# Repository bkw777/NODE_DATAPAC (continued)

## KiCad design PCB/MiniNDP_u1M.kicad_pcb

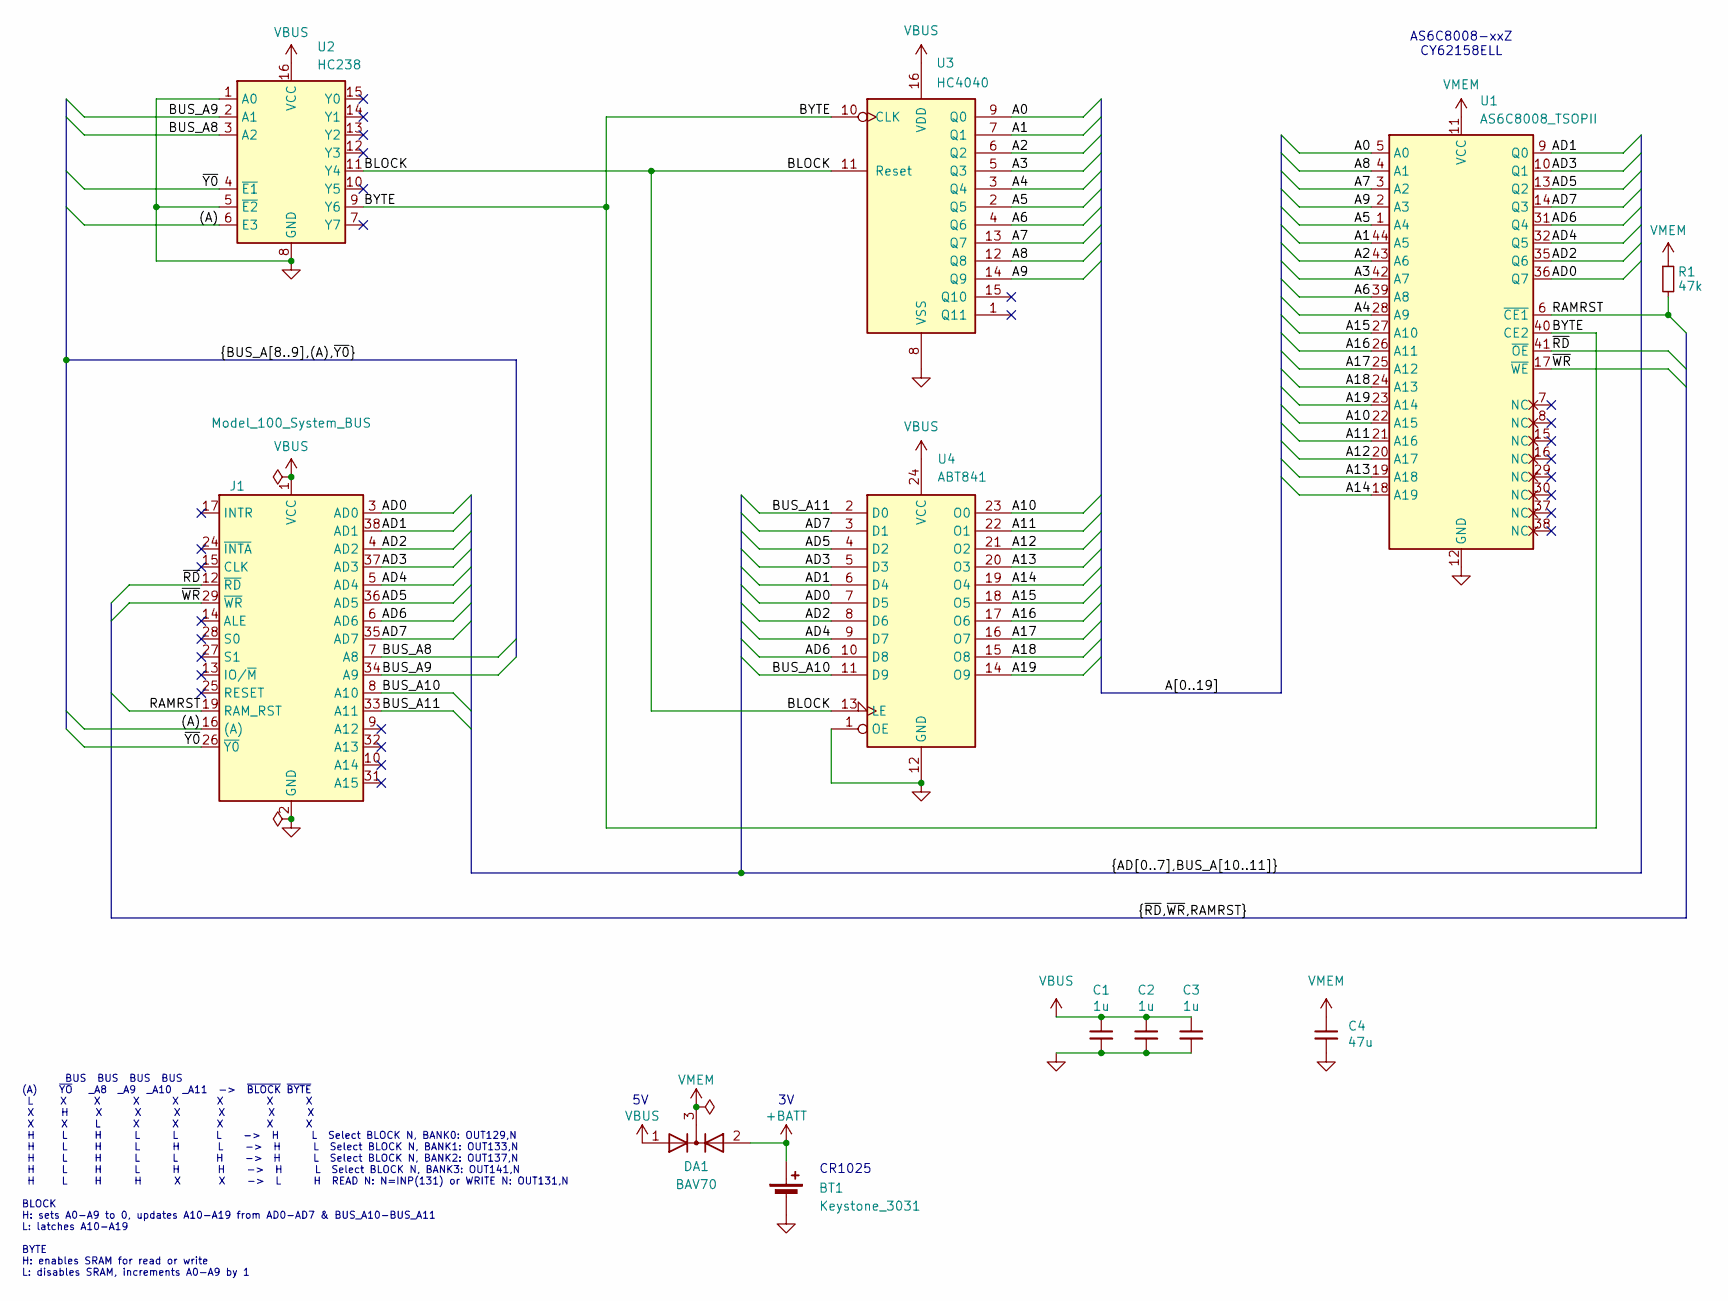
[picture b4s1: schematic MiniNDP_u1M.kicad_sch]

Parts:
BT1: Keystone_3031; MPN Keystone 3031
C1, C2, C3: 1u; C_0805; MPN CL21B105KAFNNNE
C4: 47u; C_1206; MPN C3216X5R1E476M160DC
DA1: BAV70; SOT-23; MPN BAV70-7-F
J1: Model_100_System_BUS; DIP-40_PCB; MPN 920-0172-01
R1: 47k; R_0805; MPN RMCF0805FT47K0
U1: AS6C8008_TSOPII; TSOP-II-44; MPN AS6C8008-55ZIN
U2: HC238; TSSOP-16; MPN 74HC238PW,118
U3: HC4040; TSSOP-16; MPN 74HC4040PW,118
U4: ABT841; TSSOP-24; MPN SN74ABT841APW

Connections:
+BATT: BT1.1 (+), DA1.2 (A)
/(A): J1.16 ((A)), U2.6 (E3)
/A0: U1.5 (A0), U3.9 (Q0)
/A1: U1.44 (A5), U3.7 (Q1)
/A2: U1.43 (A6), U3.6 (Q2)
/A3: U1.42 (A7), U3.5 (Q3)
/A4: U1.28 (A9), U3.3 (Q4)
/A5: U1.1 (A4), U3.2 (Q5)
/A6: U1.39 (A8), U3.4 (Q6)
/A7: U1.3 (A2), U3.13 (Q7)
/A8: U1.4 (A1), U3.12 (Q8)
/A9: U1.2 (A3), U3.14 (Q9)
/A10: U1.22 (A15), U4.23 (O0)
/A11: U1.21 (A16), U4.22 (O1)
/A12: U1.20 (A17), U4.21 (O2)
/A13: U1.19 (A18), U4.20 (O3)
/A14: U1.18 (A19), U4.19 (O4)
/A15: U1.27 (A10), U4.18 (O5)
/A16: U1.26 (A11), U4.17 (O6)
/A17: U1.25 (A12), U4.16 (O7)
/A18: U1.24 (A13), U4.15 (O8)
/A19: U1.23 (A14), U4.14 (O9)
/AD0: J1.3 (AD0), U1.36 (Q7), U4.7 (D5)
/AD1: J1.38 (AD1), U1.9 (Q0), U4.6 (D4)
/AD2: J1.4 (AD2), U1.35 (Q6), U4.8 (D6)
/AD3: J1.37 (AD3), U1.10 (Q1), U4.5 (D3)
/AD4: J1.5 (AD4), U1.32 (Q5), U4.9 (D7)
/AD5: J1.36 (AD5), U1.13 (Q2), U4.4 (D2)
/AD6: J1.6 (AD6), U1.31 (Q4), U4.10 (D8)
/AD7: J1.35 (AD7), U1.14 (Q3), U4.3 (D1)
/BLOCK: U2.11 (Y4), U3.11 (Reset), U4.13 (LE)
/BUS_A8: J1.7 (A8), U2.3 (A2)
/BUS_A9: J1.34 (A9), U2.2 (A1)
/BUS_A10: J1.8 (A10), U4.11 (D9)
/BUS_A11: J1.33 (A11), U4.2 (D0)
/BYTE: U1.40 (CE2), U2.9 (Y6), U3.10 (CLK)
/RAMRST: J1.19 (RAM_RST), R1.2, U1.6 (~CE1)
/~RD: J1.12 (~RD), U1.41 (~OE)
/~WR: J1.29 (~WR), U1.17 (~WE)
/~Y0: J1.26 (~Y0), U2.4 (~E1)
GND: BT1.2 (-), C1.2, C2.2, C3.2, C4.2, J1.2 (GND), J1.11 (GND), J1.18 (GND), J1.23 (GND), J1.30 (GND), J1.39 (GND), U1.12 (GND), U1.34 (GND), U2.1 (A0), U2.5 (~E2), U2.8 (GND), U3.8 (VSS), U4.1 (OE), U4.12 (GND)
VBUS: C1.1, C2.1, C3.1, DA1.1 (A), J1.1 (VCC), J1.40 (VCC), U2.16 (VCC), U3.16 (VDD), U4.24 (VCC)
VMEM: C4.1, DA1.3 (K), R1.1, U1.11 (VCC), U1.33 (VCC)

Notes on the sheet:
AS6C8008-xxZ CY62158ELL
BUS BUS BUS BUS (A) ~{YO} _A8 _A9 _A10 _A11 -> ~{BLOCK} ~{BYTE} L X X X X X X X X H X X X X X X X X L X X X X X H L H L L L -> H L Select BLOCK N, BANK0: OUT129,N H L H L H L -> H L Select BLOCK N, BANK1: OUT133,N H L H L L H -> H L Select BLOCK N, BANK2: OUT137,N H L H L H H -> H L Select BLOCK N,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
CR1025

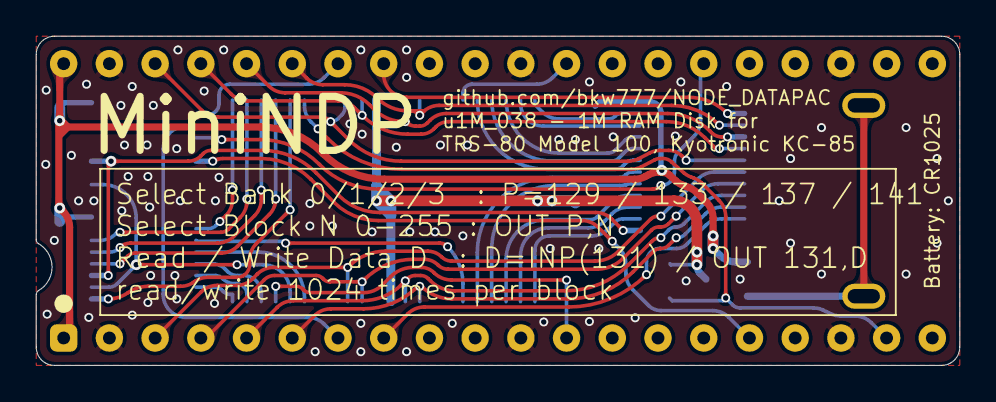
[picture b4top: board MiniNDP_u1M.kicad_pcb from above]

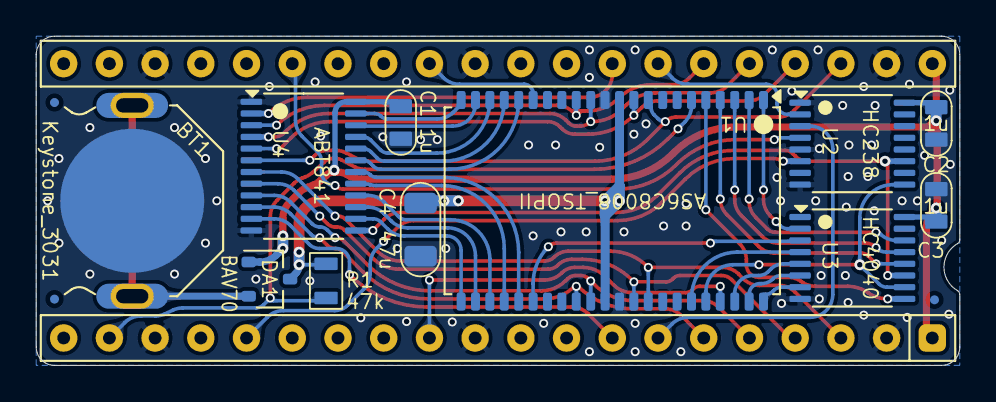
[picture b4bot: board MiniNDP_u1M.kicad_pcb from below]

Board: 2 copper layers, 51.3 x 18.3 mm, 15 parts (15 on the bottom side), 43 nets.

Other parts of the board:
F1, F2, F3: Fiducial_0.5_1.0

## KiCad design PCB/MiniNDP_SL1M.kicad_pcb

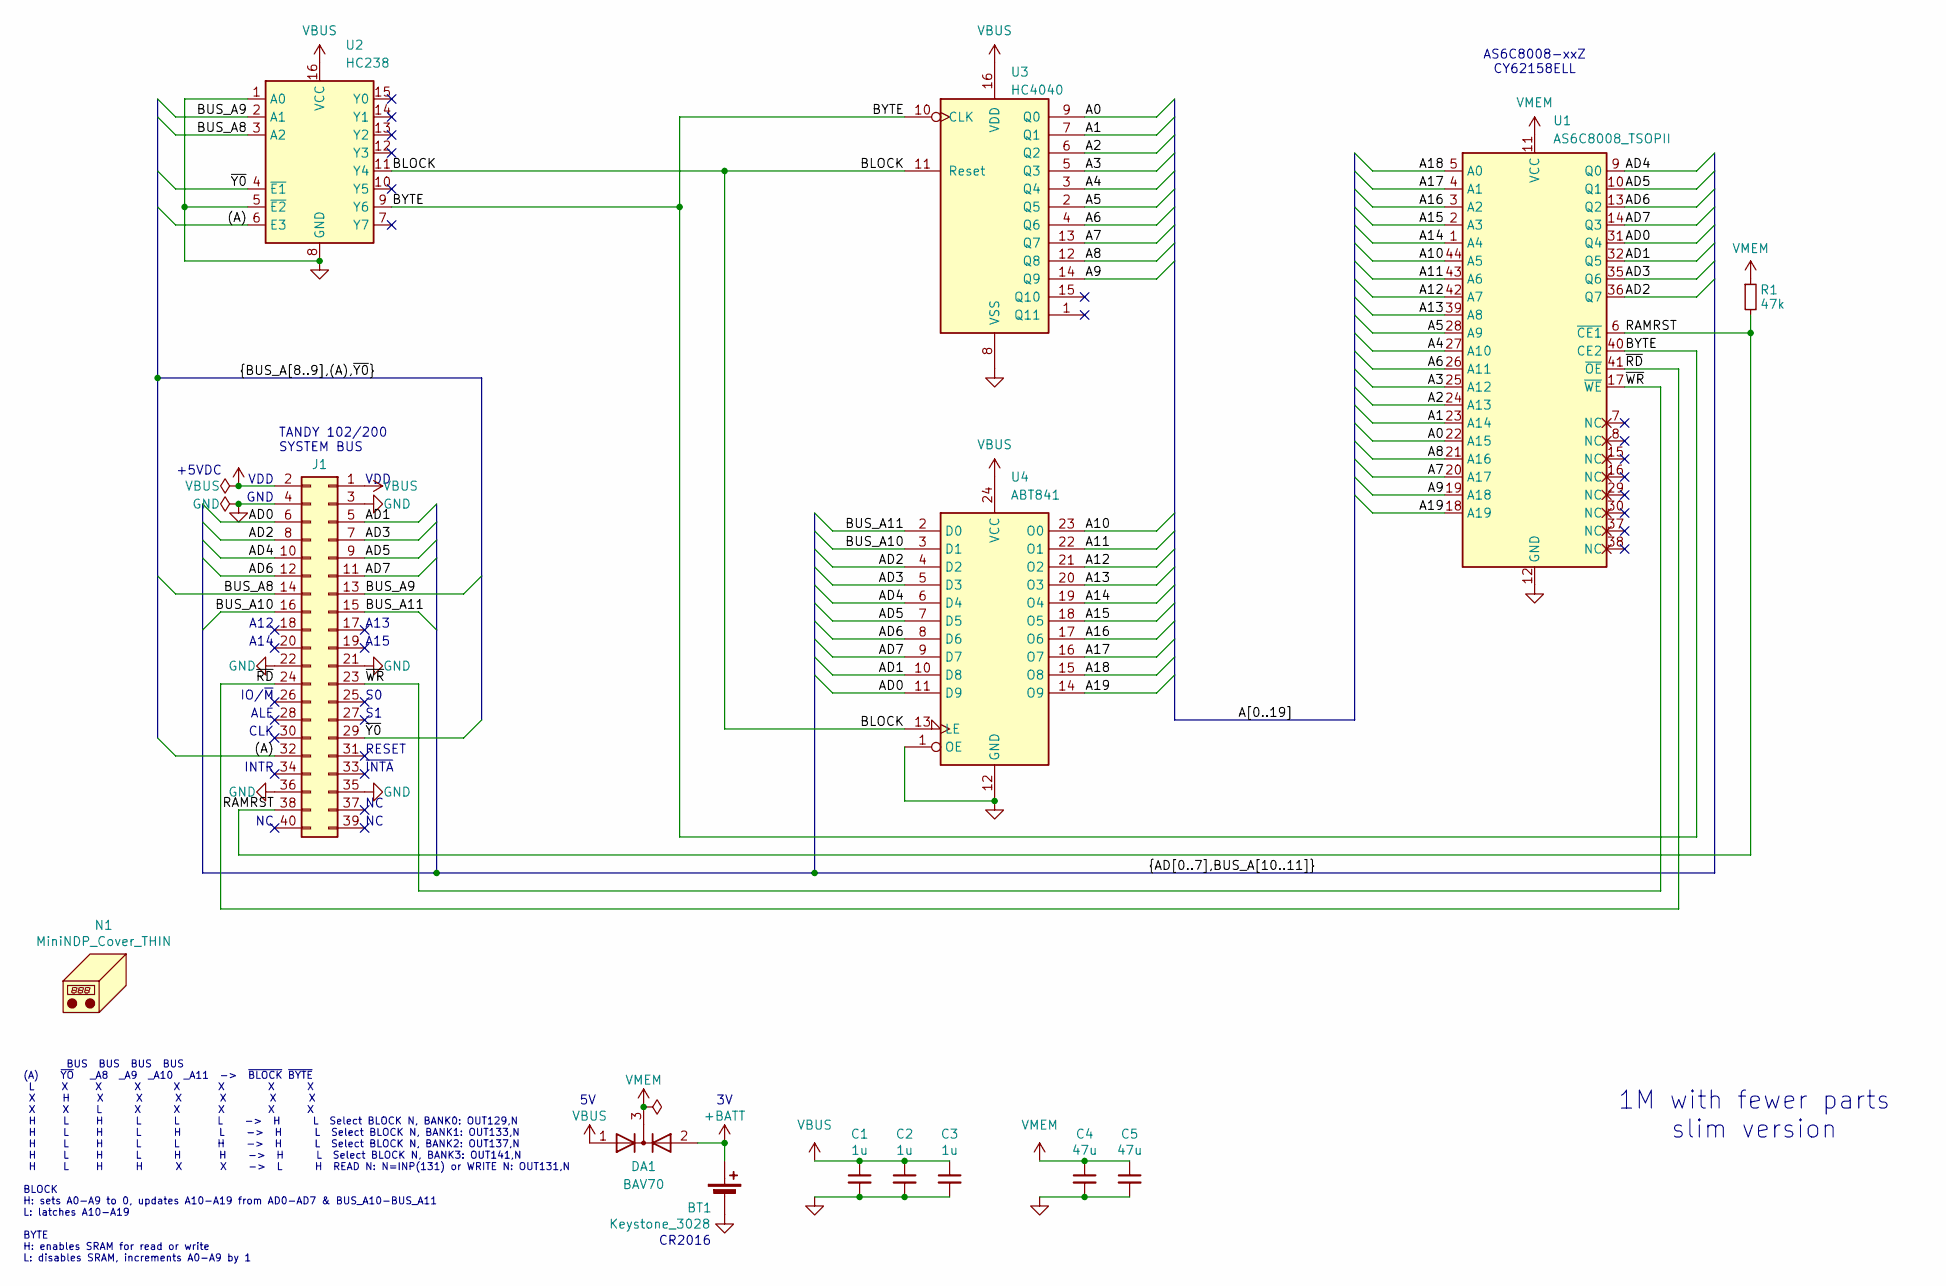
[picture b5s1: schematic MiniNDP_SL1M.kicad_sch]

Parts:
BT1: Keystone_3028; Keystone_3028_3034_bkw; MPN Keystone 3028
C1, C2, C3: 1u; C_0805; MPN CL21B105KAFNNNE
C4, C5: 47u; C_1206; MPN C3216X5R1E476M160DC
DA1: BAV70; SOT-23; MPN BAV70-7-F
J1: Conn_02x20_Odd_Even; IDC-Header_2x20_P2.54mm_Vertical; MPN 302-S401
N1: MiniNDP_Cover_THIN; MPN MiniNDP_Cover.stl
R1: 47k; R_0805; MPN RMCF0805FT47K0
U1: AS6C8008_TSOPII; TSOP-II-44; MPN AS6C8008-55ZIN
U2: HC238; TSSOP-16; MPN 74HC238PW,118
U3: HC4040; TSSOP-16; MPN 74HC4040PW,118
U4: ABT841; TSSOP-24; MPN SN74ABT841APW

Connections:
+BATT: BT1.1 (+), DA1.2 (A)
/(A): J1.32, U2.6 (E3)
/A0: U1.22 (A15), U3.9 (Q0)
/A1: U1.23 (A14), U3.7 (Q1)
/A2: U1.24 (A13), U3.6 (Q2)
/A3: U1.25 (A12), U3.5 (Q3)
/A4: U1.27 (A10), U3.3 (Q4)
/A5: U1.28 (A9), U3.2 (Q5)
/A6: U1.26 (A11), U3.4 (Q6)
/A7: U1.20 (A17), U3.13 (Q7)
/A8: U1.21 (A16), U3.12 (Q8)
/A9: U1.19 (A18), U3.14 (Q9)
/A10: U1.44 (A5), U4.23 (O0)
/A11: U1.43 (A6), U4.22 (O1)
/A12: U1.42 (A7), U4.21 (O2)
/A13: U1.39 (A8), U4.20 (O3)
/A14: U1.1 (A4), U4.19 (O4)
/A15: U1.2 (A3), U4.18 (O5)
/A16: U1.3 (A2), U4.17 (O6)
/A17: U1.4 (A1), U4.16 (O7)
/A18: U1.5 (A0), U4.15 (O8)
/A19: U1.18 (A19), U4.14 (O9)
/AD0: J1.6, U1.31 (Q4), U4.11 (D9)
/AD1: J1.5, U1.32 (Q5), U4.10 (D8)
/AD2: J1.8, U1.36 (Q7), U4.4 (D2)
/AD3: J1.7, U1.35 (Q6), U4.5 (D3)
/AD4: J1.10, U1.9 (Q0), U4.6 (D4)
/AD5: J1.9, U1.10 (Q1), U4.7 (D5)
/AD6: J1.12, U1.13 (Q2), U4.8 (D6)
/AD7: J1.11, U1.14 (Q3), U4.9 (D7)
/BLOCK: U2.11 (Y4), U3.11 (Reset), U4.13 (LE)
/BUS_A8: J1.14, U2.3 (A2)
/BUS_A9: J1.13, U2.2 (A1)
/BUS_A10: J1.16, U4.3 (D1)
/BUS_A11: J1.15, U4.2 (D0)
/BYTE: U1.40 (CE2), U2.9 (Y6), U3.10 (CLK)
/RAMRST: J1.38, R1.2, U1.6 (~CE1)
/~RD: J1.24, U1.41 (~OE)
/~WR: J1.23, U1.17 (~WE)
/~Y0: J1.29, U2.4 (~E1)
GND: BT1.2 (-), C1.2, C2.2, C3.2, C4.2, C5.2, J1.3, J1.4, J1.21, J1.22, J1.35, J1.36, U1.12 (GND), U1.34 (GND), U2.1 (A0), U2.5 (~E2), U2.8 (GND), U3.8 (VSS), U4.1 (OE), U4.12 (GND)
VBUS: C1.1, C2.1, C3.1, DA1.1 (A), J1.1, J1.2, U2.16 (VCC), U3.16 (VDD), U4.24 (VCC)
VMEM: C4.1, C5.1, DA1.3 (K), R1.1, U1.11 (VCC), U1.33 (VCC)

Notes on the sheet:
TANDY 102/200 SYSTEM BUS
+5VDC
A15
CR2016
INTR
A14
ALE
~{INTA}
CLK
GND
IO/~{M}
VDD
BUS BUS BUS BUS (A) ~{YO} _A8 _A9 _A10 _A11 -> ~{BLOCK} ~{BYTE} L X X X X X X X X H X X X X X X X X L X X X X X H L H L L L -> H L Select BLOCK N, BANK0: OUT129,N H L H L H L -> H L Select BLOCK N, BANK1: OUT133,N H L H L L H -> H L Select BLOCK N, BANK2: OUT137,N H L H L H H -> H L Select BLOCK N,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
RESET
AS6C8008-xxZ CY62158ELL
A13
A12
1M with fewer parts slim version

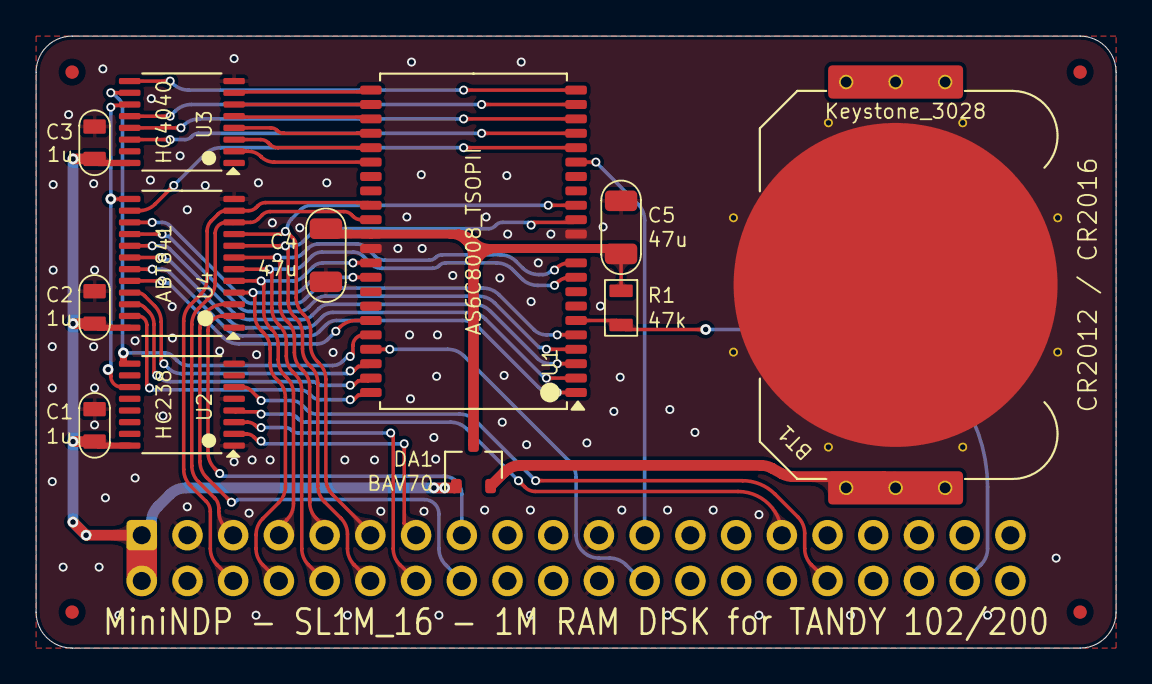
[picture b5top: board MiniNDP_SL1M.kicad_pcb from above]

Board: 2 copper layers, 60.0 x 34.0 mm, 18 parts (1 on the bottom side), 43 nets.

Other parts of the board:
F3, F3#2, F3#3, F3#4: Fiducial_0.75_1.5

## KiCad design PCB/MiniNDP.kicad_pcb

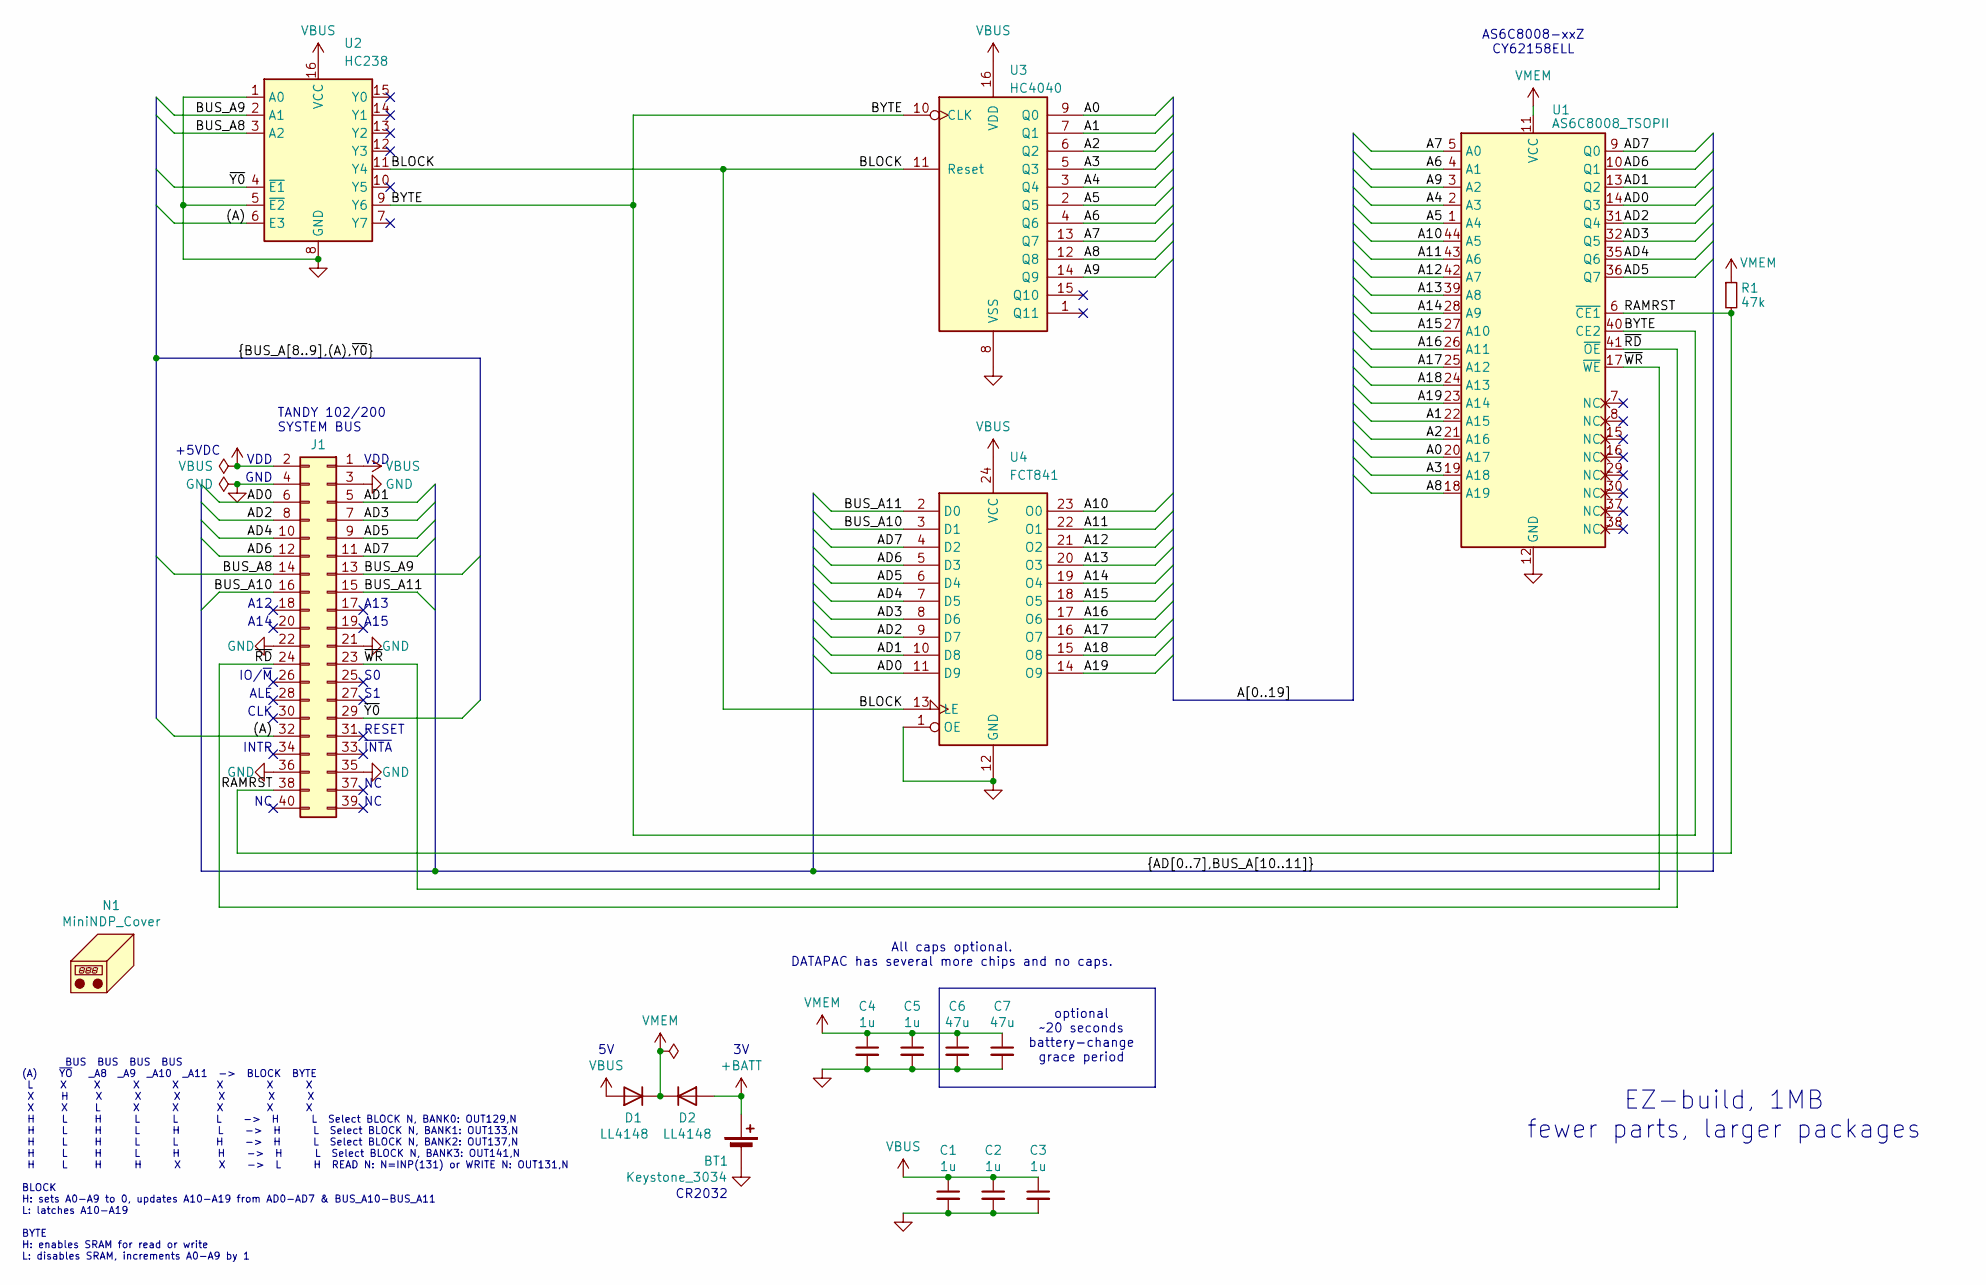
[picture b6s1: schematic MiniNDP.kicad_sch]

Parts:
BT1: Keystone_3034; Keystone_3028_3034_bkw; MPN Keystone 3034
C1, C2, C3, C4, C5: 1u; C_0805; MPN CL21B105KAFNNNE
C6, C7: 47u; C_1206; MPN C3216X5R1E476M160DC
D1, D2: LL4148; D_MiniMELF; MPN FDLL4148
J1: Conn_02x20_Odd_Even; IDC-Header_2x20_P2.54mm_Vertical; MPN 302-S401
N1: MiniNDP_Cover; MPN MiniNDP_Cover.stl
R1: 47k; R_0805; MPN RMCF0805FT47K0
U1: AS6C8008_TSOPII; TSOP-II-44; MPN AS6C8008-55ZIN
U2: HC238; SOIC-16_3.9x9.9mm_P1.27mm; MPN 74HC238D,653
U3: HC4040; SOIC-16_3.9x9.9mm_P1.27mm; MPN 74HC4040D,653
U4: FCT841; SOIC-24; MPN CY74FCT841CTSOC

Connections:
+BATT: BT1.1 (+), D2.2 (A)
/(A): J1.32, U2.6 (E3)
/A0: U1.20 (A17), U3.9 (Q0)
/A1: U1.22 (A15), U3.7 (Q1)
/A2: U1.21 (A16), U3.6 (Q2)
/A3: U1.19 (A18), U3.5 (Q3)
/A4: U1.2 (A3), U3.3 (Q4)
/A5: U1.1 (A4), U3.2 (Q5)
/A6: U1.4 (A1), U3.4 (Q6)
/A7: U1.5 (A0), U3.13 (Q7)
/A8: U1.18 (A19), U3.12 (Q8)
/A9: U1.3 (A2), U3.14 (Q9)
/A10: U1.44 (A5), U4.23 (O0)
/A11: U1.43 (A6), U4.22 (O1)
/A12: U1.42 (A7), U4.21 (O2)
/A13: U1.39 (A8), U4.20 (O3)
/A14: U1.28 (A9), U4.19 (O4)
/A15: U1.27 (A10), U4.18 (O5)
/A16: U1.26 (A11), U4.17 (O6)
/A17: U1.25 (A12), U4.16 (O7)
/A18: U1.24 (A13), U4.15 (O8)
/A19: U1.23 (A14), U4.14 (O9)
/AD0: J1.6, U1.14 (Q3), U4.11 (D9)
/AD1: J1.5, U1.13 (Q2), U4.10 (D8)
/AD2: J1.8, U1.31 (Q4), U4.9 (D7)
/AD3: J1.7, U1.32 (Q5), U4.8 (D6)
/AD4: J1.10, U1.35 (Q6), U4.7 (D5)
/AD5: J1.9, U1.36 (Q7), U4.6 (D4)
/AD6: J1.12, U1.10 (Q1), U4.5 (D3)
/AD7: J1.11, U1.9 (Q0), U4.4 (D2)
/BLOCK: U2.11 (Y4), U3.11 (Reset), U4.13 (LE)
/BUS_A8: J1.14, U2.3 (A2)
/BUS_A9: J1.13, U2.2 (A1)
/BUS_A10: J1.16, U4.3 (D1)
/BUS_A11: J1.15, U4.2 (D0)
/BYTE: U1.40 (CE2), U2.9 (Y6), U3.10 (CLK)
/RAMRST: J1.38, R1.2, U1.6 (~CE1)
/~RD: J1.24, U1.41 (~OE)
/~WR: J1.23, U1.17 (~WE)
/~Y0: J1.29, U2.4 (~E1)
GND: BT1.2 (-), C1.2, C2.2, C3.2, C4.2, C5.2, C6.2, C7.2, J1.3, J1.4, J1.21, J1.22, J1.35, J1.36, U1.12 (GND), U1.34 (GND), U2.1 (A0), U2.5 (~E2), U2.8 (GND), U3.8 (VSS), U4.1 (OE), U4.12 (GND)
VBUS: C1.1, C2.1, C3.1, D1.2 (A), J1.1, J1.2, U2.16 (VCC), U3.16 (VDD), U4.24 (VCC)
VMEM: C4.1, C5.1, C6.1, C7.1, D1.1 (K), D2.1 (K), R1.1, U1.11 (VCC), U1.33 (VCC)

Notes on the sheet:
TANDY 102/200 SYSTEM BUS
+5VDC
A15
optional ~20 seconds battery-change grace period
CR2032
INTR
A14
ALE
AS6C8008-xxZ CY62158ELL
~{INTA}
CLK
GND
IO/~{M}
VDD
All caps optional. DATAPAC has several more chips and no caps.
BUS BUS BUS BUS (A) ~{YO} _A8 _A9 _A10 _A11 -> BLOCK BYTE L X X X X X X X X H X X X X X X X X L X X X X X H L H L L L -> H L Select BLOCK N, BANK0: OUT129,N H L H L H L -> H L Select BLOCK N, BANK1: OUT133,N H L H L L H -> H L Select BLOCK N, BANK2: OUT137,N H L H L H H -> H L Select BLOCK N, BANK3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
RESET
A13
A12
EZ-build, 1MB fewer parts, larger packages

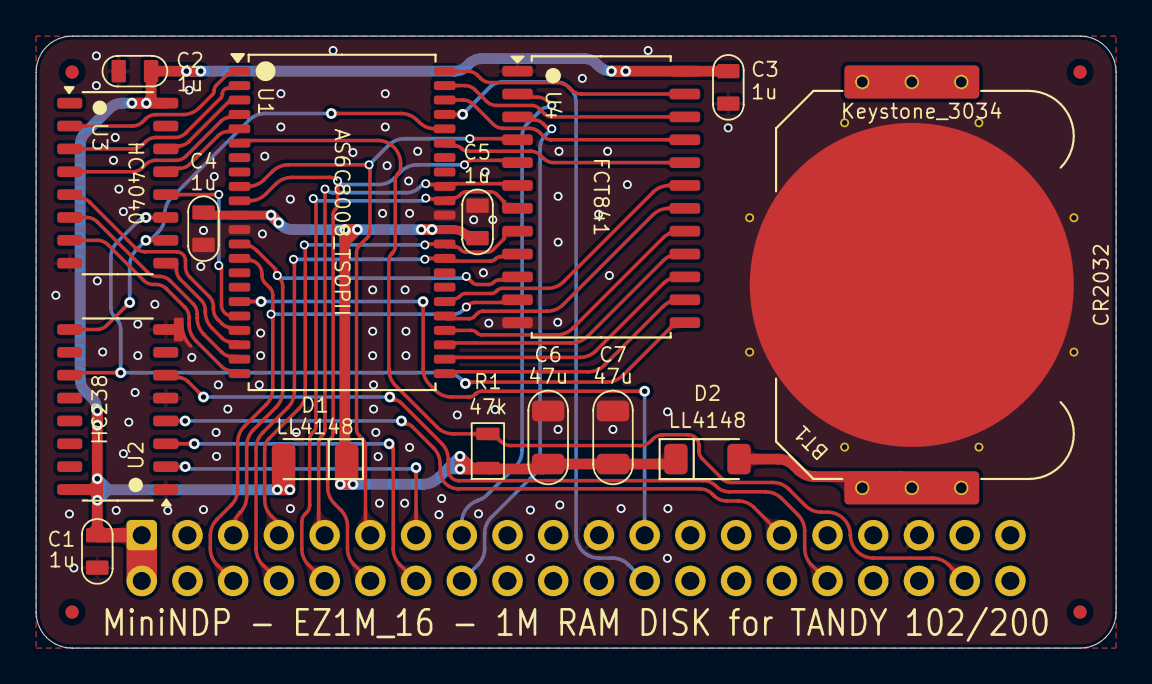
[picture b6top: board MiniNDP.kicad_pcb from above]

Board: 2 copper layers, 60.0 x 34.0 mm, 21 parts (1 on the bottom side), 43 nets.

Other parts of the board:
F2, F2#2, F3, F3#2: Fiducial_0.75_1.5

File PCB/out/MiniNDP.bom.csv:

"Reference","Value","Datasheet","Footprint","Qty","DNP","MPN","Description"
"BT1","Keystone_3034","datasheets/Keystone_3034.pdf","000_LOCAL:Keystone_3028_3034","1","","Keystone 3034","SMT 20mm x 3.2mm coin cell holder"
"C1,C2,C3,C4,C5","1u","datasheets/CL21B105KAFNNNE.pdf","000_LOCAL:C_0805","5","","CL21B105KAFNNNE","CAP CER 1UF 25V X7R 0805"
"C6,C7","47u","datasheets/TDK_MLCC_Cxxxx.pdf","000_LOCAL:C_1206","2","","C3216X5R1E476M160DC","CAP CER 47UF 25V X5R 1206"
"D1,D2","LL4148","datasheets/ll4148.pdf","000_LOCAL:D_MiniMELF","2","","FDLL4148","50V 1A General Purpose Rectifier Diode"
"J1","Conn_02x20_Odd_Even","datasheets/2x20_male_boxed.pdf","000_LOCAL:IDC-Header_2x20_P2.54mm_Vertical","1","","302-S401","CONN HEADER VERT 40POS 2.54MM"
"R1","47k","datasheets/sei-rmcf_rmcp.pdf","000_LOCAL:R_0805","1","","RMCF0805FT47K0","RES 47K OHM 1% 1/8W 0805"
"U1","AS6C8008_TSOPII","datasheets/AS6C8008.pdf","000_LOCAL:TSOP-II-44","1","","AS6C8008-55ZIN","IC SRAM 1Mx8 PARALLEL 5v TSOP-II-44"
"U2","HC238","datasheets/HC238.pdf","000_LOCAL:SOIC-16_3.9x9.9mm_P1.27mm","1","","74HC238D,653","IC DECODER/DEMUX 1 X 3:8 16SO"
"U3","HC4040","datasheets/4040.pdf","000_LOCAL:SOIC-16_3.9x9.9mm_P1.27mm","1","","74HC4040D,653","IC BINARY COUNTER 12-BIT 16SO"
"U4","FCT841","datasheets/FCT841.pdf","000_LOCAL:SOIC-24","1","","CY74FCT841CTSOC","IC 10BIT LATCH 3-STATE 24-SOIC"

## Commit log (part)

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2024-05-28 1M_B & 512_B
2024-05-28 fix 128k compatibility, AD7->A17->pin9
2024-05-28 rename 1M_B to 1M
2024-05-28 remove redundant user.dwg
2024-06-13 Add pullup on /WR. Tighter cover fit.
2024-06-13 Update BOM
2024-06-16 Add type D board, fewer larger parts
2024-06-16 D board routing
2024-06-19 E board
2024-06-21 E02 position HC574
2024-07-03 E board minor trace positions
2024-07-20 config vars in cover scad
2024-11-15 512_E & 1M silkscreen, MPNs in sch, pos & bom
2024-11-15 512_B make TSSOP-16 easier to hand solder
2024-11-19 make E version default, easier to solder
2024-11-20 larger parts on D version and proper bom
2024-11-20 readme
2024-11-20 D U6 solid gnd zone attach
2024-11-21 bootstrap info
2024-11-22 256k F board for easiest diy build
2024-11-23 comments in 256_F sch
2024-11-23 add 512k_F board using FCT841 & 2G00
2024-11-24 512k F easy build
2024-11-24 512k F sch plot
2024-11-25 refill
2024-11-25 soic footprints, 138-238 sch
2024-11-26 512k G board - all large 1206 & soic
2024-11-26 512_G missing trace ramrst to nand
2024-11-26 replace 512_F with 512_G
2024-11-26 drop redundant B & D versions from readme
2024-11-26 512-F re-add ramrst diode, both-F remove /WR pullup
2024-11-27 1M_C 1 meg based on 4040
2024-11-27 1M_C pwr & gnd traces
2024-11-27 512_F 1M_C remove ramrst diode, 1u caps
2024-11-29 easy boards add 47u cap, remove ramrst diode
2024-11-29 pics
2024-11-30 notes in historical, big cap in 1M_C
2024-12-01 pics of cover
2024-12-01 alternate 256k sram part
2024-12-01 readme about covers
2024-12-01 bundle code font
2024-12-08 update pcb models for cover
2024-12-09 comments & pics
2024-12-10 1M_C move passives around
2024-12-12 256_F wrong sram part# on silkscreen
2024-12-12 readme 256_F available sram parts
2024-12-12 256_F back pic
2024-12-13 add SL1M, rename 1M_C to EZ1M, remove 256_F & 512_F from readme
2024-12-13 default MiniNDP version silkscreen & pics
2024-12-14 EZ1M is tested
2024-12-14 touch up notes in historical schematic
2024-12-14 touch up ez1m schematic
2024-12-17 make EZ1M the default
2024-12-23 remove junk files
2024-12-23 add some datasheets
2024-12-23 re-add inrush resistor to EZ1M_tant
2024-12-23 ez1m rear silkscreen programming reference
2024-12-23 ez1m pics
2024-12-24 rename 512_F to EZ512
2025-01-08 remove EZ1M_tant, silkscreen
2025-01-09 silkscreen, pics
2025-01-09 polish EZ512
2025-01-10 rename 256_F to EZ256
2025-01-10 silkscreen & pics
2025-10-02 add historical part numbers found on a 1987 unit
2025-10-05 add NODE ROM v1.04
2025-10-05 pic of rom
2025-11-21 embed code font in pcb, bom export filename variables, delete extra battery trace
2025-11-21 silkscreen, renders
2026-04-27 ez1m pics, ram100.do/ram200.do new encoding
2026-04-29 add ChipNDP
2026-04-29 readme chipndp 4-layer pcb
2026-04-30 chipndp pcb layout
2026-05-02 chipndp 4 layer to 2 layer pcb
2026-05-02 chipndp pcb routing tweaks, ground connections
2026-05-02 chipndp pcb routing tweaks
2026-05-02 chipndp pcb routing
2026-05-03 ChipNDP 006
2026-05-04 ChipNDP 007
2026-05-04 ChipNDP 008
2026-05-04 ChipNDP 009 rotate ram chip for /WR /RD
2026-05-04 ChipNDP 010
2026-05-04 ChipNDP pics
2026-05-04 ChipNDP r012
2026-05-05 ChipNDP r014
2026-05-05 ChipNDP r016
2026-05-05 rename ChipNDP -> MiniNDP_u1M
2026-05-05 u1M sch neaten
2026-05-06 u1M silkscreen & some pcb nudges
2026-05-06 u1M 020
2026-05-06 u1M silkscreen
2026-05-07 u1M 022
2026-05-10 start disassembling RAM100.CO
2026-05-10 RAM100 diassembly
2026-05-14 RAMDSK disassembly translated from z80 to 8085
2026-05-15 u1M 023 trivial pcb polish
2026-05-15 RAMDSK disassembly automatic len,header, org
2026-05-15 RAMDSK disassembly
2026-05-15 github syntax highlighting for .S85
2026-05-18 RAM100 disassembly add make install, .DO, .map
2026-05-20 RAM100 disassembly
2026-05-20 RAM100/4-bank - support all 4 banks on MiniNDP
2026-05-20 RAM100 disasm & 4-bank code comments
2026-05-23 RAM100 4-bank alt bank logic
2026-05-25 RAM200.CO disassembly
2026-05-25 RAM100 RAM200 assembly consolidation
2026-05-25 RAMDSK makefiles minor syntax fix
2026-05-25 RAMDSK consolidated source for 100 & 200
2026-05-27 Add KC-85. Not working.
2026-05-27 RAMDSK.S85 labels
2026-05-27 RAMDSK add 4-bank support into the new common shared source
2026-05-28 WORKING KC-85
2026-05-28 RAMDSK source readme
2026-05-29 remove obsoleted ram100 4-bank
2026-05-29 K85.S85 KC7 verified
2026-05-29 RAMDSK small cleanups
2026-05-30 add RAM200v1 assembly, organize legacy bins, asm, makefiles
2026-05-30 split legacy asm to seperate orig/disasm dirs, remove legacy IFDEFS from main asm
2026-05-30 ramdsk comments, labels, makefile opts
2026-05-30 update rom_map_100_k85.txt, thanks Jeff Birt
2026-05-30 ramdsk code formatting
2026-05-30 100-k85 map
2026-05-30 ramdsk fix NBANKS<=2
2026-05-31 SL1M tiny adjust traces & teardrops
2026-05-31 EZ1M_06 move vias outside battery terminal
2026-05-31 regen loaders with updated co2ba for crlf
2026-05-31 RAMDSK makefile RBOOT.* *.calls
2026-05-31 u1M in KC-85 pics
2026-06-01 readme organization
2026-06-03 work around z88dk bug, only accepts zilog syntax for RST
2026-06-04 RAMDSK src uglier but more compatible asm formatting
2026-06-06 ramdsk src k85 rom map
2026-06-10 centralize rom map & other programming support at github/bkw777/m100_dev
2026-06-19 ramdsk annotation
2026-06-20 ramdsk src: annotation, remove dead code, optional bin size reduction
2026-06-21 ramdsk src annotation
2026-06-21 ramdsk - move 10-byte file header buffer from binary to altlcd
2026-06-22 ramdsk src - more annotation, remove more dead code
2026-06-22 ramdsk src
